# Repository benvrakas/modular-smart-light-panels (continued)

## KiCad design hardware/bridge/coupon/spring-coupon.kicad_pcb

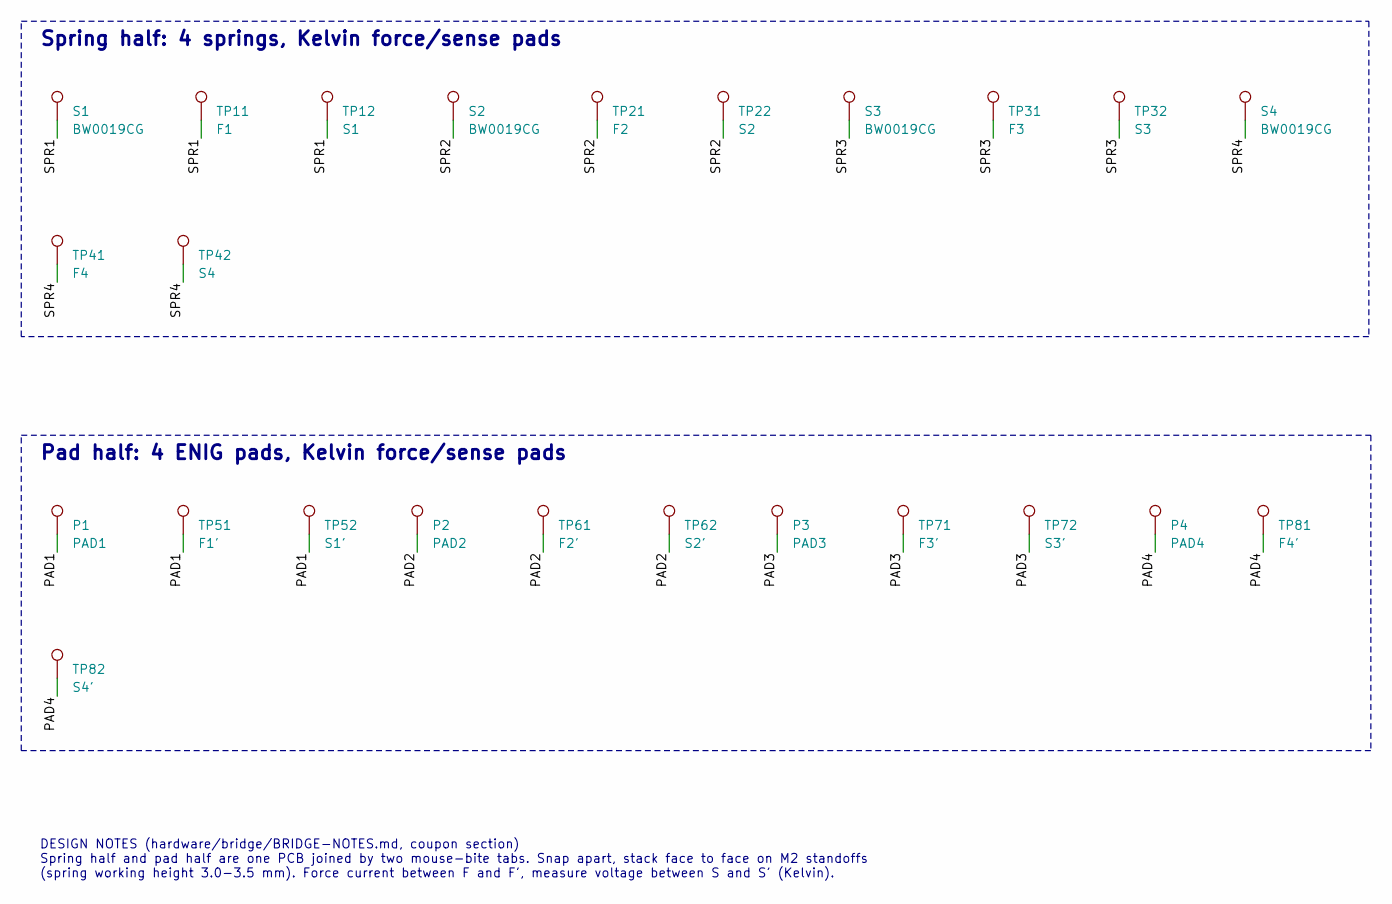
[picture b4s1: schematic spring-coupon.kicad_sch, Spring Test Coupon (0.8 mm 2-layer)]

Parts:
P1: PAD1; ContactPad_3x6
P2: PAD2; ContactPad_3x6
P3: PAD3; ContactPad_3x6
P4: PAD4; ContactPad_3x6
S1, S2, S3, S4: BW0019CG; Spring_BW0019CG; MPN BW0019CG-L3.5W1.5H4.3; LCSC C2826517
TP11: F1; TestPoint_THTPad_D2.0mm_Drill1.0mm
TP12: S1; TestPoint_THTPad_D2.0mm_Drill1.0mm
TP21: F2; TestPoint_THTPad_D2.0mm_Drill1.0mm
TP22: S2; TestPoint_THTPad_D2.0mm_Drill1.0mm
TP31: F3; TestPoint_THTPad_D2.0mm_Drill1.0mm
TP32: S3; TestPoint_THTPad_D2.0mm_Drill1.0mm
TP41: F4; TestPoint_THTPad_D2.0mm_Drill1.0mm
TP42: S4; TestPoint_THTPad_D2.0mm_Drill1.0mm
TP51: F1'; TestPoint_THTPad_D2.0mm_Drill1.0mm
TP52: S1'; TestPoint_THTPad_D2.0mm_Drill1.0mm
TP61: F2'; TestPoint_THTPad_D2.0mm_Drill1.0mm
TP62: S2'; TestPoint_THTPad_D2.0mm_Drill1.0mm
TP71: F3'; TestPoint_THTPad_D2.0mm_Drill1.0mm
TP72: S3'; TestPoint_THTPad_D2.0mm_Drill1.0mm
TP81: F4'; TestPoint_THTPad_D2.0mm_Drill1.0mm
TP82: S4'; TestPoint_THTPad_D2.0mm_Drill1.0mm

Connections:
/PAD1: P1.1, TP51.1, TP52.1
/PAD2: P2.1, TP61.1, TP62.1
/PAD3: P3.1, TP71.1, TP72.1
/PAD4: P4.1, TP81.1, TP82.1
/SPR1: S1.1, TP11.1, TP12.1
/SPR2: S2.1, TP21.1, TP22.1
/SPR3: S3.1, TP31.1, TP32.1
/SPR4: S4.1, TP41.1, TP42.1

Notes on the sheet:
Spring half: 4 springs, Kelvin force/sense pads
Pad half: 4 ENIG pads, Kelvin force/sense pads
DESIGN NOTES (hardware/bridge/BRIDGE-NOTES.md, coupon section) Spring half and pad half are one PCB joined by two mouse-bite tabs. Snap apart, stack face to face on M2 standoffs (spring working height 3.0-3.5 mm). Force current between F and F', measure voltage between S and S' (Kelvin).

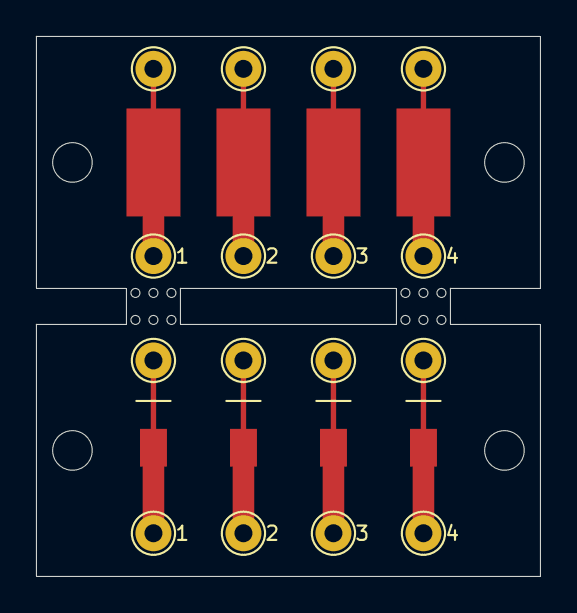
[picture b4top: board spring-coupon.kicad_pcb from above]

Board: 2 copper layers, 28.0 x 30.0 mm, 40 parts (0 on the bottom side), 8 nets.

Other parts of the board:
H1, H2, H3, H4: MountingHole_2.2mm_M2
MB1, MB2, MB3, MB4, MB5, MB6, MB7, MB8, MB9, MB10, MB11, MB12: NPTH_0.5mm

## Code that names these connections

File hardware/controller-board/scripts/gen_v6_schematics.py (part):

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    # MCU
    a(P('U1', 'CH32', {'1': 'BOOT0', '2': 'OSC_IN', '3': 'OSC_OUT', '4': 'NRST', '5': '+3V3', '6': 'LED_EN',
                       '7': 'SENSE_ADC', '8': 'UART_TX', '9': 'UART_RX', '10': 'DRIVE_EN', '11': 'CAN_STB',
                       '12': 'LED_RET', '13': 'LED_DATA', '14': 'GPIO_SPARE', '15': 'GND', '16': '+3V3',
                       '17': 'CAN_RX', '18': 'CAN_TX', '19': 'SWDIO', '20': 'SWCLK'}, B_MCU))
    a(P('Y1', 'XTAL', {'1': 'OSC_IN', '3': 'OSC_OUT', '2': 'GND', '4': 'GND'}, B_MCU))
    a(P('C5', 'C15p', {'1': 'OSC_IN', '2': 'GND'}, B_MCU))
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    a(P('R15', 'R4k7', {'1': 'BOOT0', '2': 'GND'}, B_MCU))
    # CAN
    a(P('U2', 'TCAN', {'1': 'CAN_TX', '2': 'GND', '3': '+5V', '4': 'CAN_RX', '5': '+3V3', '6': 'CANL', '7': 'CANH',
                       '8': 'CAN_STB'}, B_CAN, note='STB has an internal pull-up: standby until firmware drives PA5 low'))
    a(P('C11', 'C100n', {'1': '+5V', '2': 'GND'}, B_CAN, note='U2 VCC'))
    a(P('C24', 'C100n', {'1': '+3V3', '2': 'GND'}, B_CAN, note='U2 VIO'))
    a(P('D4', 'NUP3105', {'1': 'CANH', '2': 'CANL', '3': 'GND'}, B_CAN))
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    # joint
    a(P('J1', 'JOINT_CTL', {'1': '+36V_IN', '2': 'GND', '3': '+5V_LED', '4': 'LED_RETURN', '5': 'LED_DATA_OUT',
                            '6': 'SPARE', '7': 'CANH', '8': 'CANL', '9': 'SENSE', '10': 'DRIVE'}, B_JNT))
    a(P('R26', 'R22k', {'1': 'SPARE', '2': 'GPIO_SPARE'}, B_JNT, pop='DNP', dnp=True,
        note='DNP option: SPARE to PB1. 22k keeps a 37.8 V fault at 1.6 mA / 53 mW'))
    # buck
    a(P('F1', 'PTC050', {'1': '+36V_IN', '2': '+36V'}, B_BUCK,
        note='per-panel PTC upstream of D5: a shorted TVS or controller trips F1, not the domain fuse'))
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    a(P('R22', 'R22k', {'1': 'LED_GATE', '2': 'LED_PD'}, B_LED))
    a(P('C25', 'C22n', {'1': 'LED_GATE', '2': '+5V_LED'}, B_LED, note='gate-drain slew cap: ~0.9 ms ramp, ~0.2 A inrush'))
    a(P('Q2', '2N7002', {'1': 'LED_EN', '2': 'GND', '3': 'LED_PD'}, B_LED))
    a(P('R18', 'R100k', {'1': 'LED_EN', '2': 'GND'}, B_LED, note='holds the rail off while PA0 floats (reset/boot)'))
    a(P('U4', 'AHCT', {'1': 'GND', '2': 'LED_DATA', '3': 'GND', '4': 'LED_DATA_5V', '5': '+5V_LED'}, B_LED,
        note='powered from the switched rail: cannot back-power unpowered LEDs'))
    a(P('C15', 'C100n', {'1': '+5V_LED', '2': 'GND'}, B_LED))
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    a(P('D6', 'NUP3105', {'1': 'SENSE', '2': 'DRIVE', '3': 'GND'}, B_DISC, note='ESD on the SENSE/DRIVE buses'))
    # test pads
    for ref, net in [('TP1', 'SPARE'), ('TP2', '+3V3'), ('TP3', 'GND'), ('TP4', 'SWDIO'), ('TP5', 'SWCLK'),
                     ('TP6', 'NRST'), ('TP7', 'UART_TX'), ('TP8', 'UART_RX'), ('TP9', 'GPIO_SPARE'),
                     ('TP10', '+36V_IN'), ('TP11', '+5V'), ('TP12', '+5V_LED'), ('TP13', '+36V')]:
        a(P(ref, 'TP', {'1': net}, B_TP, value=net))
    # power flags: nets that carry power_in pins but no power_out pin
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# --------------------------------------------------------------------------------------- notes
CTRL_NOTES = """DESIGN NOTES (details and calculations: hardware/controller-board/SCHEMATIC-NOTES.md)
1. All parts on ONE side (F.Cu = wall side). B.Cu is plain white solder mask (back reflector). Joint J1 pads on F.Cu only.
2. Joint pin order 1..10: +36V GND +5V_LED LED_RETURN LED_DATA_OUT SPARE CANH CANL SENSE DRIVE.
   +36V sits at the end next to GND only (a bridge to anything else would put 36 V on a 5 V or 3.3 V net);
   DRIVE is at the far end; +5V_LED and +36V are separated by GND. Pad n meets pad n on the edge board.
3. Buck U5: 36 V -> 5 V, fsw 600 kHz (RT 162k), L 22 uH, Cout 2 x 22 uF, FB 53k6/10k2 (5.00 V), Rc 4k7 + Cc 22 nF + Chf 100 pF.
   EN open = always on. Everything on +36V is rated >= 60 V (SMAJ36A clamps at <= 58.1 V): Cin 2 x 4.7 uF 100 V, D7 100 V.
   F1 (PTC 0.5 A hold / 1 A trip / 60 V) sits between joint pad 1 (+36V_IN) and +36V, upstream of D5:
   a failed TVS or a controller short trips F1 instead of the domain fuse. TP10 = +36V_IN (jig feeds through F1), TP13 = +36V.
4. LED rail: Q1 P-MOSFET, default OFF (R21 pull-up, R18 holds Q2 off while PA0 floats). C25 sets a ~0.9 ms soft start.
   U4 runs from +5V_LED, so LED data cannot back-power unlit LEDs.
   Firmware: blank the LEDs before switching the rail off (the off-ramp is ~3-6 ms).
5. DRIVE: Q3 open-drain + R11 1k. With Q3 off, a sustained 36 V short on DRIVE draws no current. While Q3 pulls low into such
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   into 3V3 is sunk by the U6 shunt (trips ~3.56 V; CH32V203 VDD abs max 4.0 V).
7. CAN TVS D4 NUP3105L: 36 V standoff, 40 V min breakdown (> 37.8 V bus maximum), 60 V max clamp at 6 A, 12-16 pF.
   TCAN1044V bus pins: +-58 V.
8. R26 (SPARE -> PB1) is DNP. JP1 CAN termination is open, closed only on the segment's far-end node."""

PASSIVE_NOTES = """DESIGN NOTES (V6, decisions 0009/0010; details: hardware/controller-board/SCHEMATIC-NOTES.md)
1. All edge boards are this one passive design. The bus is +36V (decision 0019). The LEDs and their decoupling sit on +5V_LED, the switched rail
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
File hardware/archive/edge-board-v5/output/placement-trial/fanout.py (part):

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add_via('+3V3', -25.4, 13.6); add_track('+3V3', F, [pad('C9', '1'), (-25.4, 13.6)], 0.3)
add_track('+3V3', B, [(-25.4, 13.6), (-25.8, 13.2), (-25.8, 1.7)], 0.3); add_via('+3V3', -25.8, 1.7)
add_track('+3V3', F, [(-25.8, 1.7), (-25.35, 1.25), (-12.9, 1.25)], 0.3)
# CAN_RS: U1.11 -> via under U1 -> B.Cu SE, north of CAN_RX, under the +3V3 spine corner -> the CAN_RS via above the strip
add_track('/CAN_RS', F, [pad('U1', '11'), (-19.1, 18.12), (-18.9, 17.92), (-18.9, 16.95)], 0.25); add_via('/CAN_RS', -18.9, 16.95)
add_track('/CAN_RS', B, [(-18.9, 16.95), (-13.95, 12.0), (-11.2, 12.0), (-8.3, 9.1)], 0.25)
# Over U1's top-left (pin swap LED_RET <-> LED_EN, decision 0008):
#  LED_RET: U1.12 straight to R7.2 / R8.1 (top row, west) on F.Cu
add_track('/LED_RET', F, [pad('U1', '12'), (-21.6, 17.47), (-23.83, 17.47), pad('R7', '2')], 0.25)
add_track('/LED_RET', F, [pad('R8', '1'), (-23.83, pad('R8', '1')[1])], 0.25)
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add_track('/SENSE_ADC', F, [(-7.9, 16.34), (-7.64, 16.6), (-7.64, 17.25), pad('D2', '3')], 0.25)
#  D3.1 (GND) is boxed in by SENSE_ADC and +3V3: via at the outer end of its own pad (via in pad, decision 0007)
add_via('GND', -10.05, 16.92)
#  DRIVE_GPIO (U1.10) -> D3.3 straight east under SENSE_ADC's neck (Freerouting does U1.10 -> R11)
add_track('/DRIVE_GPIO', F, [pad('U1', '10'), (-14.51, 18.0), (-12.37, 18.0), pad('D3', '3')], 0.2)
#  LED_DATA: U1.13 -> via west of U1 -> B.Cu west (y 14.4) and down x -27.7 -> via -> F.Cu between U4's pins 4/5,
#  under its body into U4.2 (the level shifter's input faces away from the MCU)
add_track('/LED_DATA', F, [pad('U1', '13'), (-21.3, 16.83), (-21.6, 16.45)], 0.25); add_via('/LED_DATA', -21.6, 16.45)
add_track('/LED_DATA', B, [(-21.6, 16.45), (-22.5, 14.4), (-27.7, 14.4), (-27.7, 9.95)], 0.25); add_via('/LED_DATA', -27.7, 9.95)
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add_track('GND', F, [pad('U2', '2'), (-13.8, pad('U2', '2')[1])], 0.4)
# ---------------------------------------------------------------- U1 escape (hand-routed; Freerouting jams here)
# Bottom escape into the strip test pads, each through its own gap in the J1 in-pad via row (y 7.65):
#   gap W (x < -23.9): SWDIO | gap A (X1|X2): SWCLK, GPIO_SPARE, UART_RX | gap B (X2|X3): UART_TX, NRST
# Left-column pins SWCLK/SWDIO leave west; GPIO_SPARE/UART/NRST leave under the body (F.Cu, x -17.5..-15.95).
add_track('/SWCLK', F, [pad('U1', '20'), (-21.6, 12.28), (-21.6, 9.6), (-20.75, 8.75), (-20.75, 6.35), pad('TP5', '1')], 0.25)
add_track('/SWDIO', F, [pad('U1', '19'), (-22.1, 12.92), (-22.1, 10.6), (-24.4, 8.3), (-24.4, 2.54), pad('TP4', '1')], 0.25)
add_track('/GPIO_SPARE', F, [pad('U1', '14'), (-17.5, 16.17), (-17.5, 11.3), (-20.25, 8.55), (-20.25, 3.3), pad('TP9', '1')], 0.25)
add_track('/UART_RX', F, [pad('U1', '9'), (-16.9, 17.47), (-16.9, 11.0), (-19.75, 8.15), (-19.75, 7.6), pad('TP8', '1')], 0.25)
add_track('/UART_TX', F, [pad('U1', '8'), (-16.45, 16.83), (-16.45, 9.6), (-15.7, 8.85), (-15.7, 7.0), pad('TP7', '1')], 0.25)
add_track('/NRST', F, [pad('U1', '4'), (-15.95, 14.22), (-15.95, 11.0), (-15.2, 10.25), (-15.2, 4.7), (-17.0, 4.7),
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# U1 supply pins west to C7/C9 (C9's GND pad gets the via; no vias in the +5V corridor under U1)
add_track('+3V3', F, [pad('U1', '16'), (-21.5, 14.88), pad('C7', '1'), pad('C9', '1')], 0.3)
add_track('GND', F, [pad('U1', '15'), (-21.5, 15.53), pad('C7', '2'), pad('C9', '2')], 0.3)
report.append('U1 escape: SWD/UART/GPIO/NRST to the strip TPs, CAN_TX/RX on B.Cu, supply pins to C7/C9')

# ---------------------------------------------------------------- 4. buck (LAYOUT-NOTES 6, 13): explicit copper
add_track('/BUCK_SW', F, [pad('U5', '2'), pad('L1', '1')], 0.6)                      # SW: ~1.9 mm, pad to L1 only
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
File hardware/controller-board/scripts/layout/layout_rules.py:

"""Controller board: net classes and board rules (into controller-board.kicad_pro) and custom DRC rules
(controller-board.kicad_dru). Plain Python, re-runnable; only touches the keys it owns.

usage:  python layout_rules.py            (paths are fixed relative to this script)

JLCPCB 4-layer limits used (JLC04161H-7628, 1.6 mm, 1 oz outer / 0.5 oz inner):
  track/space >= 0.09 mm (we use 0.2 nominal; 0.1 mm minimum for autorouter neck-downs), via drill >= 0.15 (we use 0.3 / 0.6 pad), copper to edge >= 0.2-0.3 mm.
"""
import json
import os

HERE = os.path.dirname(os.path.abspath(__file__))
PRJ = os.path.normpath(os.path.join(HERE, '..', '..'))
PRO = os.path.join(PRJ, 'controller-board.kicad_pro')
DRU = os.path.join(PRJ, 'controller-board.kicad_dru')

# Nets that may sit next to +36V copper (SPEC 2, decision 0011): GND and the 36 V-tolerant nets.
# BUCK_SW / BUCK_BOOT swing to 24-29 V themselves (they are the U5 pins beside VIN).
TOLERANT = ['GND', '/CANH', '/CANL', '/SPARE', '/SENSE', '/DRIVE', '/BUCK_SW', '/BUCK_BOOT',
            'unconnected-(U5-EN-Pad3)']  # U5 EN is open; it sits beside VIN inside the IC pinout, no copper on it
HV = ['+36V', '/+36V_IN']

with open(PRO, encoding='utf-8') as f:
    p = json.load(f)
ns = p.setdefault('net_settings', {})
ns.setdefault('meta', {'version': 4})
classes = ns.setdefault('classes', [])
default = next((c for c in classes if c['name'] == 'Default'), None)
default.update(track_width=0.2, clearance=0.2, via_diameter=0.6, via_drill=0.3)


def cls(name, track, clearance=0.2, prio=0):
    c = dict(default)
    c.update(name=name, track_width=track, clearance=clearance, via_diameter=0.6, via_drill=0.3, priority=prio)
    return c


ns['classes'] = [default,
                 cls('HV36', 0.6, prio=0),     # +36V, +36V_IN: <= 0.3 A, but short and wide (TVS / C_IN paths)
                 cls('Power', 0.5, prio=1),    # GND, +5V (1 A), +5V_LED (0.73 A)
                 cls('Supply', 0.3, prio=2),   # +3V3 (< 0.1 A)
                 cls('Switch', 0.8, prio=3)]   # BUCK_SW: hand-routed / poured, kept small
ns['netclass_patterns'] = (
    [{'netclass': 'HV36', 'pattern': n} for n in HV] +
    [{'netclass': 'Power', 'pattern': n} for n in ('GND', '+5V', '+5V_LED')] +
    [{'netclass': 'Supply', 'pattern': '+3V3'}, {'netclass': 'Switch', 'pattern': '/BUCK_SW'}])
ns['netclass_assignments'] = None

ds = p.setdefault('board', {}).setdefault('design_settings', {})
ds['track_widths'] = [0.0, 0.2, 0.3, 0.4, 0.5, 0.6, 0.8, 1.0]
ds['via_dimensions'] = [{'diameter': 0.0, 'drill': 0.0}, {'diameter': 0.6, 'drill': 0.3}]
r = ds.setdefault('rules', {})
r.update(min_track_width=0.1,   # JLC 4-layer: 0.09 mm; Freerouting necks LED_RET to 0.1 mm for 0.25 mm at R8
          min_clearance=0.15, min_via_diameter=0.5, min_via_annular_width=0.1,
         min_through_hole_diameter=0.3, min_copper_edge_clearance=0.3, min_hole_clearance=0.25,
         min_hole_to_hole=0.25, min_silk_clearance=0.0, min_text_height=0.8, min_text_thickness=0.12,
         solder_mask_to_copper_clearance=0.0, use_height_for_length_calcs=True)
sev = ds.setdefault('rule_severities', {})
sev.update({'lib_footprint_issues': 'ignore', 'lib_footprint_mismatch': 'ignore'})
with open(PRO, 'w', encoding='utf-8', newline='\n') as f:
    json.dump(p, f, indent=2)
    f.write('\n')

tol = ' && '.join(f"B.NetName != '{n}'" for n in TOLERANT + HV)
with open(DRU, 'w', encoding='utf-8', newline='\n') as f:
    f.write(f'''(version 1)

# J1 joint pads run to the trapezoid base by design: the fillet to the code-0 edge board's J4 forms there
# (SCHEMATIC-NOTES 6.2, footprint ControllerJoint_ControllerEdge). Everything else keeps >= 0.3 mm.
(rule "J1 joint pads at the base edge"
  (severity ignore)
  (constraint edge_clearance (min 0mm))
  (condition "A.Type == 'Pad' && A.memberOfFootprint('J1')"))

# SPEC 2 / decision 0011: +36V copper may only sit next to GND or 36 V-tolerant nets. Everything else
# keeps >= 1.0 mm, which leaves room for the GND pour (0.25 clearance + 0.25 min width) to fill between.
(rule "+36V neighbours: GND or 36 V-tolerant only"
  (constraint clearance (min 1.0mm))
  (condition "A.NetClass == 'HV36' && {tol}"))

# Buck switch node: the TI layout rules (SCHEMATIC-NOTES 12) keep it away from the crystal and the ADC node.
(rule "SW node away from crystal / ADC"
  (constraint clearance (min 10mm))
  (condition "A.NetName == '/BUCK_SW' && (B.NetName == '/OSC_IN' || B.NetName == '/OSC_OUT' || B.NetName == '/SENSE_ADC')"))
''')
print('wrote', PRO, 'and', DRU)
